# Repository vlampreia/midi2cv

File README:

Another MIDI to CV project!
================================================================================

This project arose out of the desire to control antiquated drum machines which
respond to analogue pulses with MIDI enabled devices. MIDI to CV solutions exist
in abundance, nonetheless I saw this as an opportunity to involve myself in more
embedded software development and as an introduction to hardware development.

This project does not consider modular synthesiser CV in any way whatsoever. The
end devices this converter is targeted to drive respond to simple voltage-level
triggers, and so it lacks output voltage scaling and MIDI processing for
anything other than channel, note, and velocity parameters at this time.

SYSTEM OVERVIEW AND REQUIREMENTS
--------------------------------------------------------------------------------

At a top level, the system processes MIDI and outputs up to 8 analogue pulses
simultaneously. It must be capable of mapping channel, note, and velocity data
from MIDI packets to their respective analogue values and CV DACs as programmed
by the user, in real time and with imperceptible jitter.

MIDI channel and note to CV channel mappings are user configurable using the
front panel, which provides a 3 character display and a set of momentary
switches. User settings are stored in the MCU flash memory and persist after a
loss of power.

INTERFACE
--------------------------------------------------------------------------------

The system is abstracted into programmable CV channels. Each CV channel has a
MIDI channel and note assigned to it. Channels may also be configured to respond
to all MIDI channels and or all note values.

The user interface consists of a display showing the current mode and value, and
three buttons, one to cycle mode (CV channel, MIDI channel, and MIDI note, in
that order), and two to increment and decrement the value. The omni value can be
selected by holding down both value buttons.

FIRMWARE
--------------------------------------------------------------------------------

The MCU firmware is written in C and is listed under ./firmware.

This is currently a work in progress.

A makefile is present to facilitate building and flashing the firmware. It
targets the ATMega328P-PU using a USBASP programmer.

HARDWARE
--------------------------------------------------------------------------------

The hardware platform is designed using KiCAD and is listed under ./hardware.

This is currently a work in progress. A full BOM will be rendered once the
hardware has been finalised.

The platform consists of two boards interconnected via standard pin headers:
- The main board hosting the MCU, power and MIDI input stages, as well as the CV
  output stage.
- The HUI board hosting the display and navigation buttons.

The MCU is an ATMega328, selected for it's simplicity and active community base,
it is a fairly capable package boasting a 20MHz clock, 2KB RAM, USART and a SPI.
The 328 lacks any digital to analogue conversion, for this the 8bit MCP4802 was
selected. Each IC packages 2 DACs, addressable via SPI by the MCU.

The MIDI input stage follows the standards set out by the MIDI spec. A H11L1 was
selected for the optoisolator, which is identical to the PC900 suggested in the
spec.

Control voltage outputs are buffered internally by the DACs. Output voltage can
vary from 0v to about 4v on max gain.

Supply input is regulated and can scale from 8v to 35v.

KNOWN LIMITATIONS AND FUTURE IMPROVEMENTS
--------------------------------------------------------------------------------

- The output voltage scale is an unknown and can change from target device to
  device. The hardware currently lacks support for programmable output voltage
  scaling.

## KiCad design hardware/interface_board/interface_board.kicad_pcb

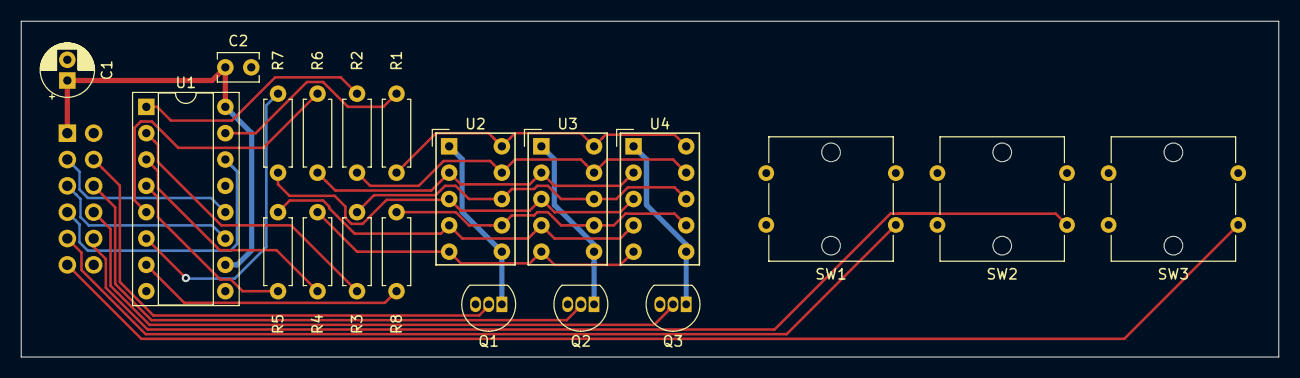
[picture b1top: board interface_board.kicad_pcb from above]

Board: 2 copper layers, 121.3 x 32.4 mm, 21 parts (1 on the bottom side), 30 nets.

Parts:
C1: 10uF; CP_Radial_D5.0mm_P2.00mm
C2: 0.1uF; C_Disc_D3.8mm_W2.6mm_P2.50mm
J1: Conn_02x06_Odd_Even; PinSocket_2x06_P2.54mm_Vertical
Q1, Q2, Q3: BC548; TO-92_Inline
R1, R2, R3, R4, R5, R6, R7, R8: R_Small_US; R_Axial_DIN0207_L6.3mm_D2.5mm_P7.62mm_Horizontal
SW1, SW2, SW3: SW_SPST; B3W-4050
U1: 74HC595; DIP-16_W7.62mm_Socket
U2, U3, U4: SC36-11SEKWA; HDSP-7401

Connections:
+5V: C1.1, C2.1, J1.1, U1.10, U1.16
/BTN_1: J1.9, SW1.1
/BTN_2: J1.10, SW2.1
/BTN_3: J1.11, SW3.1
/DISP_1_CS: J1.4, Q1.2
/DISP_2_CS: J1.6, Q2.2
/DISP_3_CS: J1.8, Q3.2
/LATCH: J1.3, U1.12
/SCLK: J1.5, U1.11
/SI: J1.7, U1.14
GND: C1.2, C2.2, J1.2, Q1.3, Q2.3, Q3.3, SW1.2, SW2.2, SW3.2, U1.8, U1.13
unnamed: Q1.1, U2.1, U2.6
unnamed: Q2.1, U3.1, U3.6
unnamed: Q3.1, U4.1, U4.6
unnamed: R1.1, U2.10, U3.10, U4.10
unnamed: R1.2, U1.15
unnamed: R2.1, U2.9, U3.9, U4.9
unnamed: R2.2, U1.1
unnamed: R3.1, U2.8, U3.8, U4.8
unnamed: R3.2, U1.2
unnamed: R4.1, U2.5, U3.5, U4.5
unnamed: R4.2, U1.3
unnamed: R5.1, U2.4, U3.4, U4.4
unnamed: R5.2, U1.4
unnamed: R6.1, U2.2, U3.2, U4.2
unnamed: R6.2, U1.5
unnamed: R7.1, U2.3, U3.3, U4.3
unnamed: R7.2, U1.6
unnamed: R8.1, U2.7, U3.7, U4.7
unnamed: R8.2, U1.7

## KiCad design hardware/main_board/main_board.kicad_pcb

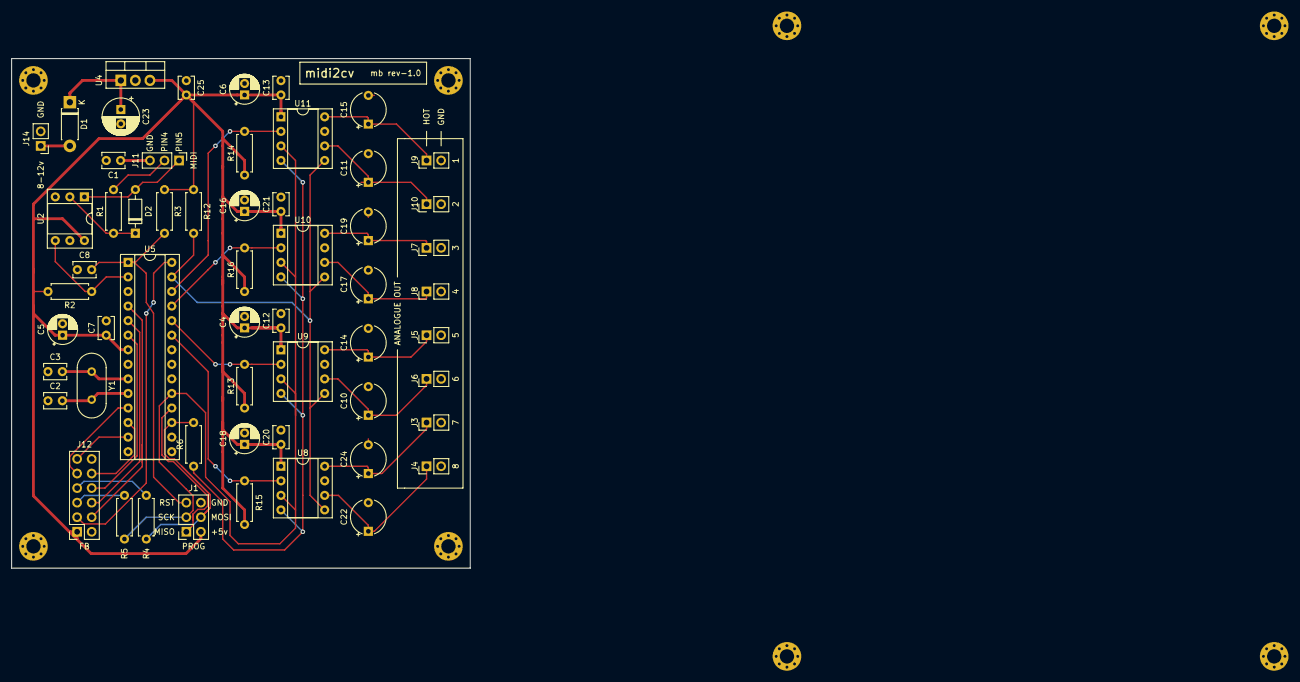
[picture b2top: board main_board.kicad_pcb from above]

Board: 2 copper layers, 80.0 x 88.9 mm, 57 parts (0 on the bottom side), 38 nets.

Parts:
C1, C7, C12, C13, C20, C21, C25: 0.1uF; C_Disc_D3.8mm_W2.6mm_P2.50mm
C2, C3: 22pF; C_Disc_D3.8mm_W2.6mm_P2.50mm
C4, C5, C6, C16, C18: 10uF; CP_Radial_D5.0mm_P2.00mm
C8: 100nF; C_Disc_D3.8mm_W2.6mm_P2.50mm
C10, C11, C14, C15, C17, C19, C22, C24: 1uF; CP_Radial_Tantal_D6.0mm_P5.00mm
C23: 0.33uF; CP_Radial_D6.3mm_P2.50mm
D1: D_ALT; D_DO-41_SOD81_P7.62mm_Horizontal
D2: 1N914; D_DO-35_SOD27_P7.62mm_Horizontal
J1: Conn_02x03_Odd_Even; PinSocket_2x03_P2.54mm_Vertical
J3, J4, J5, J6, J7, J8, J9, J10, J14: Conn_01x02; PinHeader_1x02_P2.54mm_Vertical
J11: Conn_01x02; PinHeader_1x03_P2.54mm_Vertical
J12: Conn_02x03_Odd_Even; PinSocket_2x06_P2.54mm_Vertical
R1: 220; R_Axial_DIN0207_L6.3mm_D2.5mm_P7.62mm_Horizontal
R2: 270; R_Axial_DIN0207_L6.3mm_D2.5mm_P7.62mm_Horizontal
R3, R4, R5, R6, R12, R13, R14, R15, R16: 4k7; R_Axial_DIN0207_L6.3mm_D2.5mm_P7.62mm_Horizontal
U2: H11L1; DIP-6_W7.62mm_Socket
U4: L7805; TO-220-3_Vertical
U5: ATmega328P-PU; DIP-28_W7.62mm_Socket
U8, U9, U10, U11: MCP4802; DIP-8_W7.62mm_Socket
Y1: 20MHz; Crystal_HC49-U_Vertical

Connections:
+5V: C4.1, C5.1, C6.1, C7.1, C12.1, C13.1, C16.1, C18.1, C20.1, C21.1, C25.1, J1.2, J12.1, R2.2, R3.1, R12.1, R13.1, R14.1, R15.1, R16.1, U2.6, U4.3, U5.7, U8.1, U9.1, U10.1, U11.1
/BTN_1: J12.9, U5.11
/BTN_2: J12.10, U5.12
/BTN_3: J12.11, U5.13
/CS_1: R15.2, U5.23, U8.2
/CS_2: R13.2, U5.24, U9.2
/CS_3: R16.2, U5.25, U10.2
/CS_4: R14.2, U5.26, U11.2
/DISP_1_CS: J12.4, U5.4
/DISP_2_CS: J12.6, U5.5
/DISP_3_CS: J12.8, U5.6
/LDAC: R12.2, U5.27, U8.5, U9.5, U10.5, U11.5
/LDISP: J12.3, U5.28
/MIDI_4: J11.2, R1.2
/MIDI_5: D2.2, J11.1, U2.1
/MIDI_GND: C1.1, J11.3
/MIDI_IN: R2.1, U2.4, U5.2
/MISO: J1.1, U5.18
/MOSI: J1.4, R5.2, R6.2, U5.17
/RES: C8.2, J1.5, R3.2, U5.1
/SCK: J1.3, R4.2, U5.19, U8.3, U9.3, U10.3, U11.3
/dac_section/OUT_1: C24.1, J3.1, U8.8
/dac_section/OUT_2: C22.1, J4.1, U8.6
/dac_section/OUT_3: C14.1, J5.1, U9.8
/dac_section/OUT_4: C10.1, J6.1, U9.6
/dac_section/OUT_5: C19.1, J7.1, U10.8
/dac_section/OUT_6: C17.1, J8.1, U10.6
/dac_section/OUT_7: C15.1, J9.1, U11.8
/dac_section/OUT_8: C11.1, J10.1, U11.6
/dac_section/SI: R6.1, U8.4, U9.4, U10.4, U11.4
GND: C1.2, C2.1, C3.1, C4.2, C5.2, C6.2, C7.2, C8.1, C10.2, C11.2, C12.2, C13.2, C14.2, C15.2, C16.2, C17.2, C18.2, C19.2, C20.2, C21.2, C22.2, C23.2, C24.2, C25.2, J1.6, J3.2, J4.2, J5.2, J6.2, J7.2, J8.2, J9.2, J10.2, J12.2, J14.2, U2.5, U4.2, U5.8, U5.22, U8.7, U9.7, U10.7, U11.7
unnamed: C2.2, U5.10, Y1.2
unnamed: C3.2, U5.9, Y1.1
unnamed: C23.1, D1.1, U4.1
unnamed: D1.2, J14.1
unnamed: D2.1, R1.1, U2.2
unnamed: J12.5, R4.1
unnamed: J12.7, R5.1

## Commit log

2019-08-21 firmware and hardware
2019-08-21 FW: improve doc in MCP4802 header
2019-08-21 HW: rename supply input diode value
2019-08-21 add readme
2019-08-22 fw: refactor button debounce logic
2019-08-22 fw: cleanup
2019-08-23 fw: refactor user interface into views
